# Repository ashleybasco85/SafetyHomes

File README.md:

# SafetyHomes
Distributed embedded system with low-power architecture and automated environmental logging

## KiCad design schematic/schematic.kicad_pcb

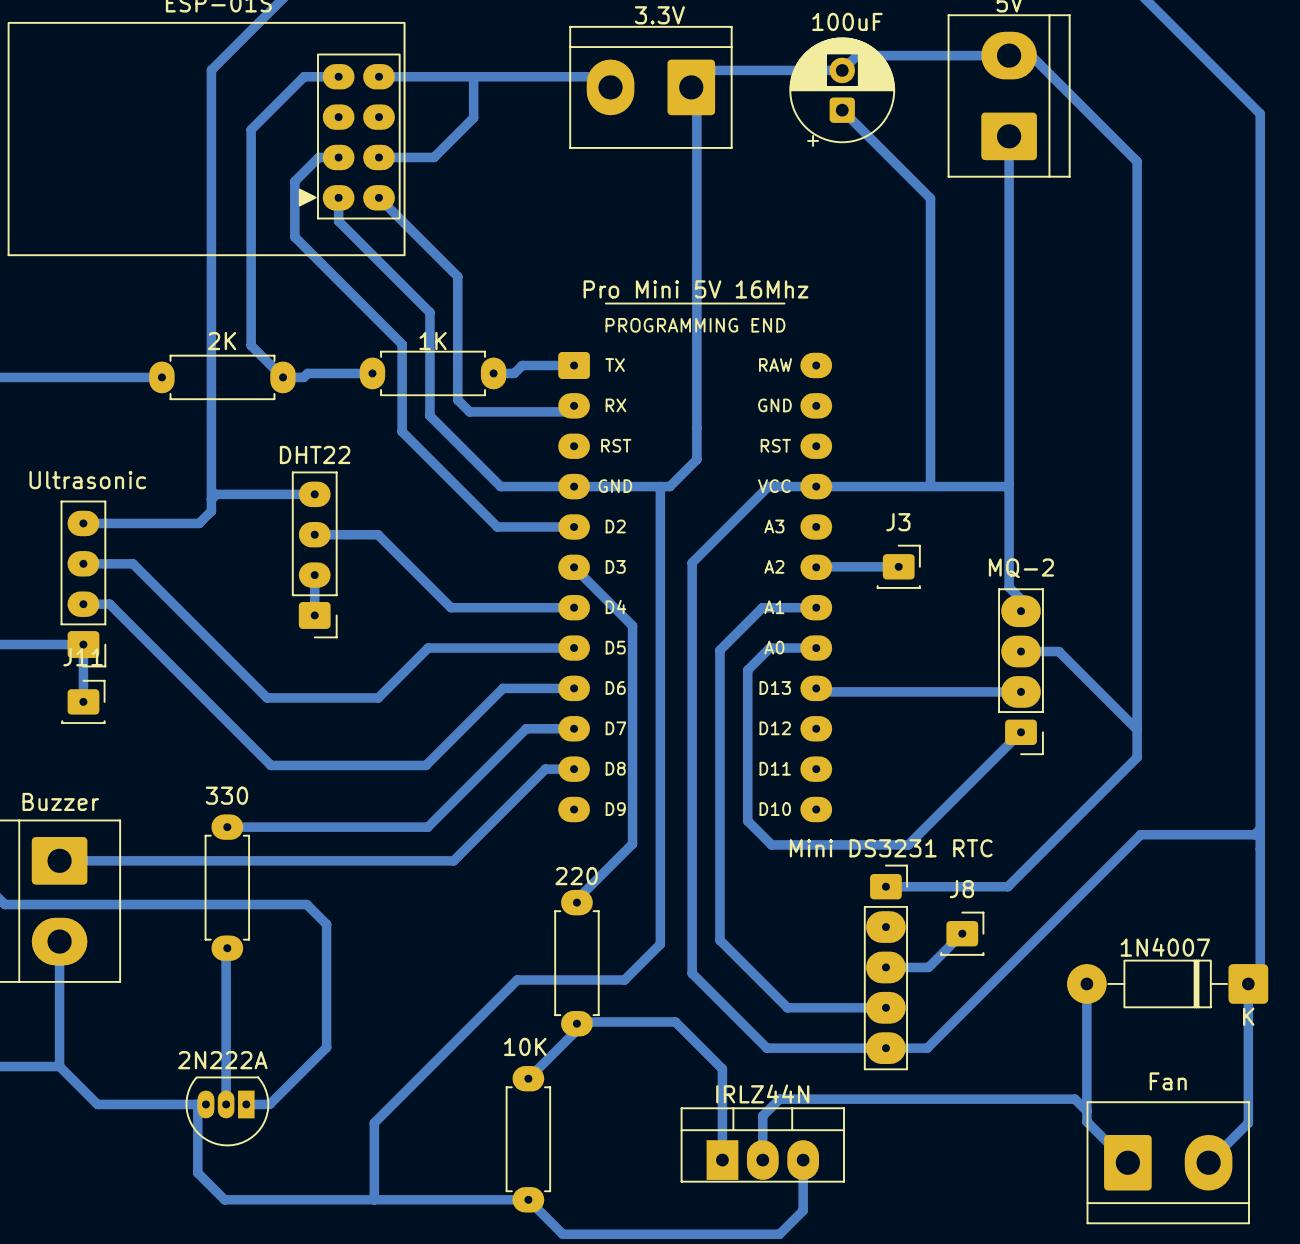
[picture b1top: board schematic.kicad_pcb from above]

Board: 2 copper layers, 22 parts (0 on the bottom side), 21 nets.

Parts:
1K: 1K; R_Axial_DIN0207_L6.3mm_D2.5mm_P7.62mm_Horizontal
1N4007: 1N4007; D_DO-41_SOD81_P10.16mm_Horizontal
2K: 2K; R_Axial_DIN0207_L6.3mm_D2.5mm_P7.62mm_Horizontal
2N222A: NPN; TO-92L_Inline
3.3V: 3.3V; TerminalBlock_bornier-2_P5.08mm
5V: 5V; TerminalBlock_bornier-2_P5.08mm
10K: 10K; R_Axial_DIN0207_L6.3mm_D2.5mm_P7.62mm_Horizontal
100uF: 100uF; CP_Radial_D6.3mm_P2.50mm
220: 220; R_Axial_DIN0207_L6.3mm_D2.5mm_P7.62mm_Horizontal
330: 330; R_Axial_DIN0207_L6.3mm_D2.5mm_P7.62mm_Horizontal
Buzzer: Buzzer; TerminalBlock_bornier-2_P5.08mm
DHT22: DHT22; PinHeader_1x04_P2.54mm_Vertical
ESP-01S: ESP-01S; ESP01S_CustomSymbol
Fan: Fan; TerminalBlock_bornier-2_P5.08mm
IRLZ44N: IRLZ44N; TO-220-3_Vertical
J3: J 5V; PinSocket_1x01_P2.54mm_Vertical
J8, J11: J1 5V; PinSocket_1x01_P2.54mm_Vertical
MQ-2: MQ-2; PinHeader_1x04_P2.54mm_Vertical
Mini DS3231 RTC: MINI DS3231 RTC; PinSocket_1x05_P2.54mm_Vertical
Pro Mini 5V 16Mhz: ProMini_5V_16MHz; ProMini_24SidePins_NoTopHeader
Ultrasonic: Ultrasonic; PinHeader_1x04_P2.54mm_Vertical

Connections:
3.3V: 3.3V.2, ESP-01S.4 (EN), ESP-01S.8 (VCC_3V3)
5V: 1N4007.1 (K), 5V.1, 100uF.1, DHT22.4, Fan.2, MQ-2.4, Mini DS3231 RTC.5, Pro Mini 5V 16Mhz.21 (VCC_5V), Ultrasonic.4
A0: MQ-2.1, Pro Mini 5V 16Mhz.17 (A0)
A1: Mini DS3231 RTC.4, Pro Mini 5V 16Mhz.18 (A1)
A2: J3.1, J8.1, Mini DS3231 RTC.3, Pro Mini 5V 16Mhz.19 (A2)
D2-GPIO2: ESP-01S.3 (GPIO2), Pro Mini 5V 16Mhz.5 (D2)
D3: 220.2, Pro Mini 5V 16Mhz.6 (D3)
D4: DHT22.3, Pro Mini 5V 16Mhz.7 (D4)
D5: Pro Mini 5V 16Mhz.8 (D5), Ultrasonic.3
D6: Pro Mini 5V 16Mhz.9 (D6), Ultrasonic.2
D7: 330.2, Pro Mini 5V 16Mhz.10 (D7)
D8: Buzzer.1 (+), Pro Mini 5V 16Mhz.11 (D8)
D13: MQ-2.2, Pro Mini 5V 16Mhz.16 (D13)
Fan_GND: 1N4007.2 (A), Fan.1, IRLZ44N.2 (D)
GND: 2K.2, 2N222A.3 (E), 3.3V.1, 5V.2, 10K.2, 100uF.2, Buzzer.2 (-), ESP-01S.1 (GND), IRLZ44N.3 (S), MQ-2.3, Mini DS3231 RTC.1, Pro Mini 5V 16Mhz.4 (GND)
GND1: 2N222A.1 (C), DHT22.1, DHT22.2, J11.1, Ultrasonic.1
unnamed: 2N222A.2 (B), 330.1
unnamed: 10K.1, 220.1, IRLZ44N.1 (G)
RX: 1K.2, 2K.1, ESP-01S.7 (RXD/GPIO3)
RX-TX: ESP-01S.2 (TXD/GPIO1), Pro Mini 5V 16Mhz.2 (D0_RX)
TX: 1K.1, Pro Mini 5V 16Mhz.1 (D1_TX)
